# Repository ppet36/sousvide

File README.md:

# DIY Sous Vide cooker

This repository contains resources for my DIY WiFi Sous Vide cooker. Repo contains
responsive Angular/Bootstrap application for setting cooking parameters and manage
cooker, Eagle PCB design w/ schematic and 3D model of enclosure.

Cooker are based on ESP12E (or ESP07) module, submersible heater PROFESSOR PO500 and
EHEIM Compact 300 aquarium pump.
For measuring temperature watertight DS18B20 sensor is used. Analog
ESP PIN is used for detecting water level and protecting "dry" run of cooker.
Some parts are printed on 3D printer, bottom part of cooker is bended aluminium
sheet.

Memory of ESP12E is divided into two parts; 1M for firmware and 3M for SPIFFS.
Application (arduino/data/*) is uploaded to ESP's SPIFFS and is served via
internal HTTP server. Firmware creates AP SousVideCooker with listening HTTP server
at:

```
http://192.168.4.1/
```

AP password is defaulted to 123456 and can be set in fw source file.

Via application can be also set PID parameters for heater. Firmware uses AutoPID
library from https://github.com/r-downing/AutoPID.
Also other Arduino libraries is used https://github.com/milesburton/Arduino-Temperature-Control-Library,
https://github.com/bblanchon/ArduinoJson ...

Heater as well as pump is driven via triacs. Duo MOC3041/BT136 is used for heater
and plain MOC3041 for pump (which is only 5W). For 500W heater is not needed
additional BT136 cooling but small TO220 heatsink is suitable.

Module is powered via 5V/1A PSU. Many of theses is on ebay; for example:
https://www.ebay.com/sch/i.html?&_nkw=High-Grade-12V-5V-24V-9V-AC-DC-Power-Supply-Buck-Converter-Step-Down-Module
You can use also 3.3V PSU instead of 5V; so linear regulator is not needed.

PCB is designed to fit on top of mounting cube. All connections (except of power supply cord)
is connected from bottom side of PCB.

(PCB in image is working prototype and not looking exactly same as in eagle/* resources;
I modified schematic and PCB layout later taking experiences into account)

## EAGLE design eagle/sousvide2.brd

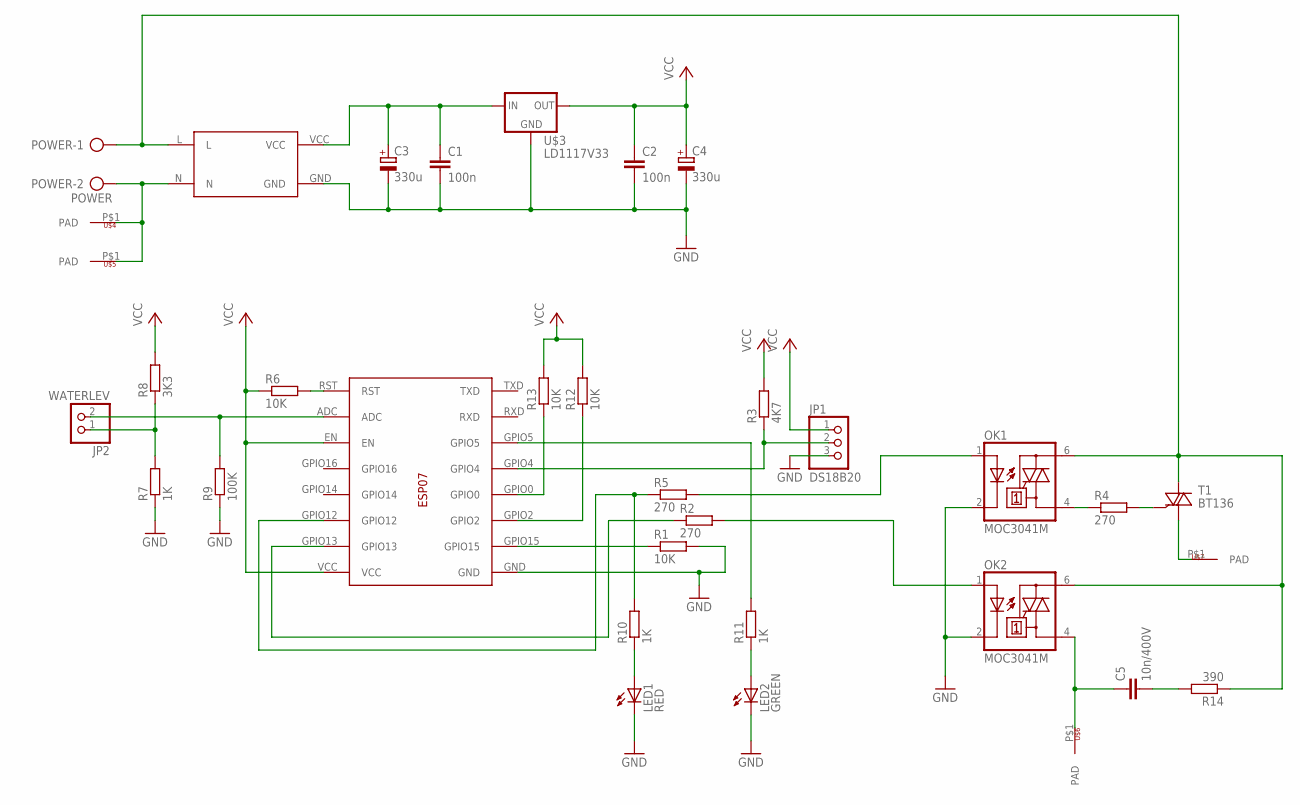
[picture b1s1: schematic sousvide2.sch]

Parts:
C1, C2: 100n; C050-025X075
C3, C4: 330u; E2,5-6
C5: 10n/400V; C102-064X133
JP1: DS18B20; 1X03
JP2: WATERLEV; 1X02
LED1: RED; LED5MM
LED2: GREEN; LED5MM
OK1, OK2: MOC3041M; DIL06
POWER: POWER; AK300/2
R1, R6, R12, R13: 10K; 0204/7
R2, R4: 270; 0204/7
R3: 4K7; 0204/7
R5: 270; 0207/12
R7, R10: 1K; 0204/7
R8: 3K3; 0204/7
R9: 100K; 0204/7
R11: 1K; 0207/10
R14: 390; 0207/7
T1: BT136; TO220AB
U$1: ESP12F; ESP07
U$2: PSU5V1A; PSU5V
U$3: LD1117V33
U$4, U$5, U$6, U$7: PAD

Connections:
GND: C1.2, C2.2, C3.-, C4.-, JP1.3, LED1.K (C), LED2.K (C), OK1.2 (C), OK2.2 (C), R1.2, R7.1, R9.1, U$1.GND, U$2.GND, U$3.GND
unnamed: R1.1, U$1.GPIO15
unnamed: R2.1, U$1.GPIO13
unnamed: OK1.4 (A1), R4.1
unnamed: R4.2, T1.3 (G)
unnamed: C1.1, C3.+, U$2.VCC, U$3.IN
unnamed: POWER.2, U$2.N, U$4.P$1, U$5.P$1
unnamed: OK1.6 (A2), OK2.6 (A2), POWER.1, R14.1, T1.2 (A2), U$2.L
unnamed: LED1.A, R10.1
unnamed: T1.1 (A1), U$7.P$1
unnamed: R13.1, U$1.GPIO0
unnamed: R5.1, R10.2, U$1.GPIO12
unnamed: OK1.1 (A), R5.2
unnamed: LED2.A, R11.1
unnamed: OK2.1 (A), R2.2
unnamed: R11.2, U$1.GPIO5
unnamed: C5.1, OK2.4 (A1), U$6.P$1
unnamed: JP1.2, R3.1, U$1.GPIO4
unnamed: R12.1, U$1.GPIO2
unnamed: R6.2, U$1.RST
unnamed: JP2.2, R9.2, U$1.ADC
unnamed: JP2.1, R7.2, R8.1
unnamed: C5.2, R14.2
VCC: C2.1, C4.+, JP1.1, R3.2, R6.1, R8.2, R12.2, R13.2, U$1.EN, U$1.VCC, U$3.OUT

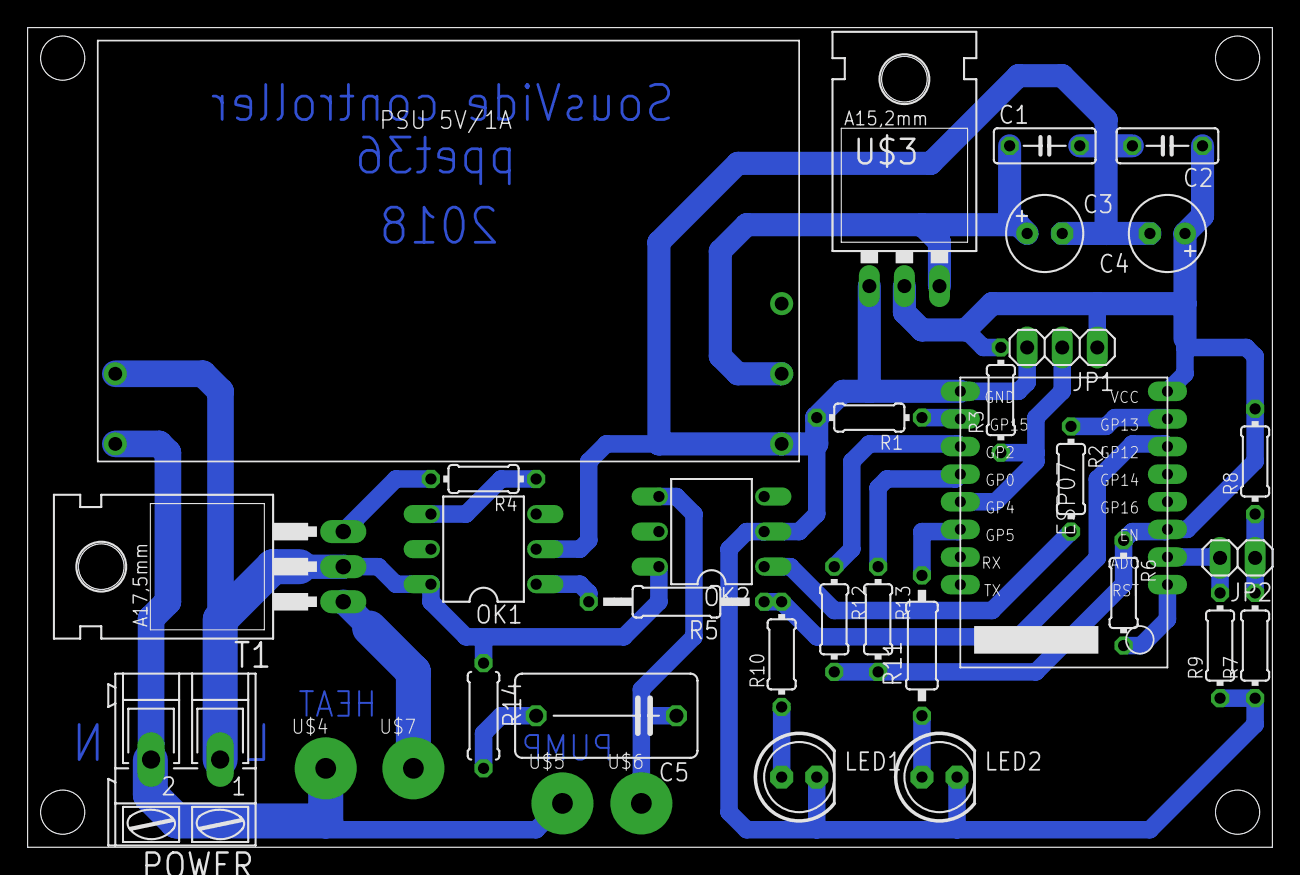
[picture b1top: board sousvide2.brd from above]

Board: 2 copper layers, 90.2 x 59.4 mm, 34 parts (0 on the bottom side), 24 nets.

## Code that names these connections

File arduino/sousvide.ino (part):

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 * Pins asignment:
 *
 * ADC     - water level sensor.
 * GPIO12  - triac switch for heater.
 * GPIO13  - triac switch for pump.
 * GPIO4   - OneWire DS18B20
 * GPIO5   - green status led.
 *
 * Code uses ArduinoJson, SPIFFS and OTA library.
 *
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
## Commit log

2018-06-20 init repository
2018-06-20 - init repository.
2018-06-20 - init
2018-06-21 corrections
